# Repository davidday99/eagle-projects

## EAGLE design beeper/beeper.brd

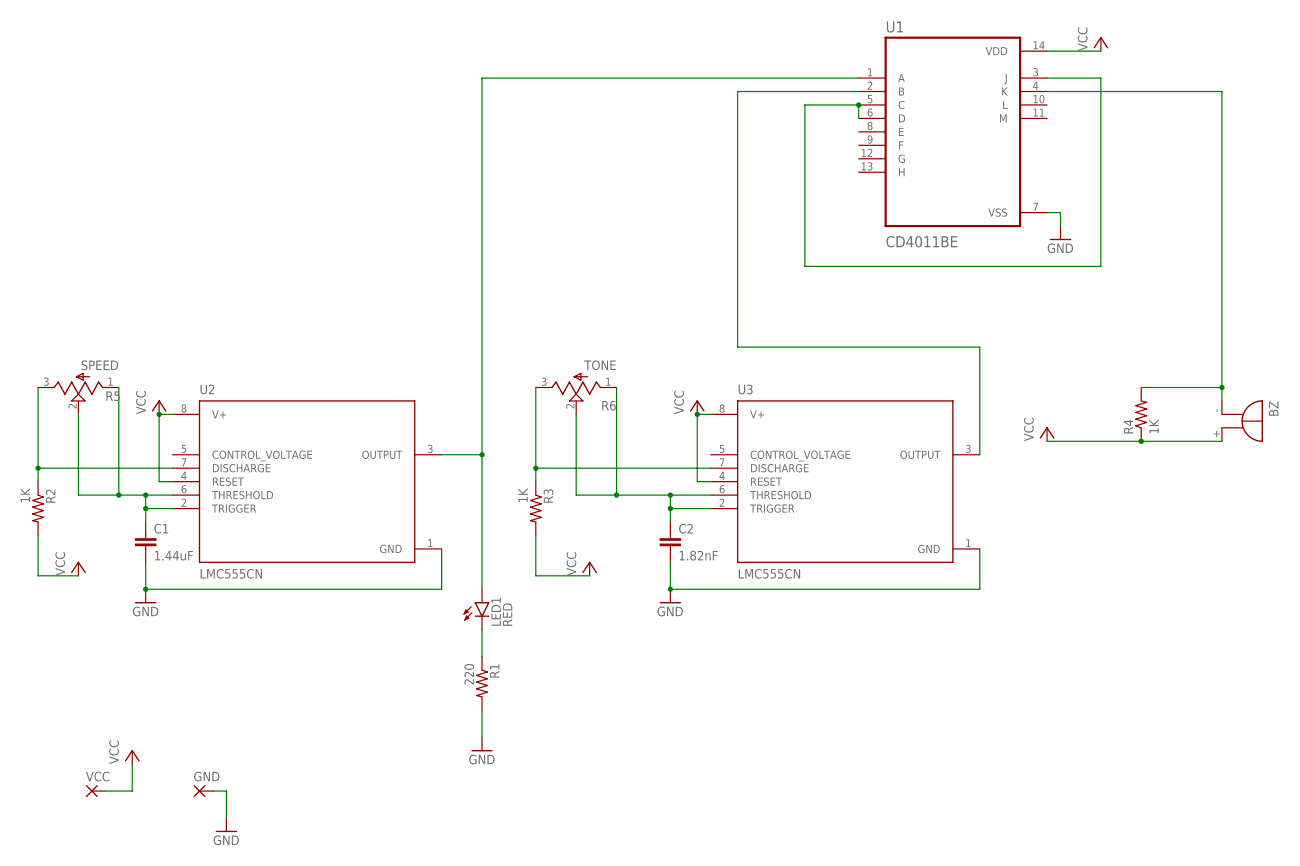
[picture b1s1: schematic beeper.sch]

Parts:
BZ: F/QMBIII; MPN AI-1440-TWT-12V-R
C1: 1.44uF; C2.5-3; MPN MPMPP250W15J0N200
C2: 1.82nF; C2.5-3; MPN FA26C0G2J182JNU00
GND: SMD2; SMD1,27-2,54
LED1: RED; LED3MM; MPN TLLR4400
R1: 220; 0204/7; MPN MCF 0.25W 220R
R2, R3, R4: 1K; 0204/7; MPN MP006904
R5: SPEED; TO250P760H635-3_PV12P105A01B00; MPN PV12P105A01B00
R6: TONE; TO250P760H635-3_PV12P105A01B00; MPN PV12P105A01B00
U1: CD4011BE; DIP794W45P254L1969H508Q14; MPN CD4011BE
U2, U3: LMC555CN; DIP794W45P254L959H508Q8; MPN LM555CN
VCC: SMD2; SMD1,27-2,54

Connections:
GND: C1.2, C2.2, GND.1, R1.2, U1.7 (VSS), U2.1 (GND), U3.1 (GND)
unnamed: R2.1, R5.3, U2.7 (DISCHARGE)
unnamed: C1.1, R5.1, R5.2, U2.2 (TRIGGER), U2.6 (THRESHOLD)
unnamed: LED1.A, U1.1 (A), U2.3 (OUTPUT)
unnamed: LED1.K (C), R1.1
unnamed: R3.1, R6.3, U3.7 (DISCHARGE)
unnamed: C2.1, R6.1, R6.2, U3.2 (TRIGGER), U3.6 (THRESHOLD)
unnamed: U1.2 (B), U3.3 (OUTPUT)
unnamed: U1.3 (J), U1.5 (C), U1.6 (D)
unnamed: BZ.- (+), R4.2, U1.4 (K)
VCC: BZ.+ (-), R2.2, R3.2, R4.1, U1.14 (VDD), U2.4 (RESET), U2.8 (V+), U3.4 (RESET), U3.8 (V+), VCC.1

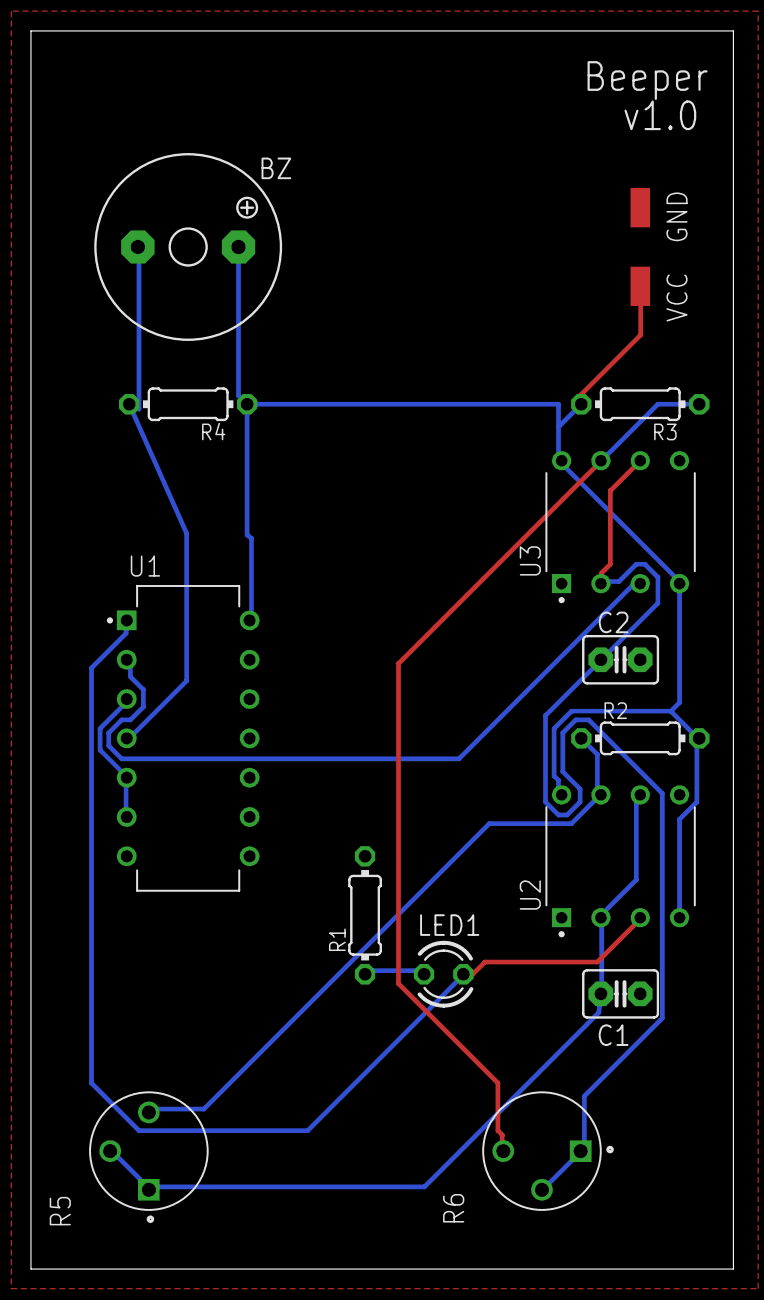
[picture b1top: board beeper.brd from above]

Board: 2 copper layers, 45.4 x 80.0 mm, 15 parts (0 on the bottom side), 11 nets.

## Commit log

2023-03-23 completed CAM
